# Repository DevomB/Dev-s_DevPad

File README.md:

# Dev's DevPad

This is my submission to HackPad to qualfiy for undercity. A 3-button macro pad with rotary encoder designed for real-world productivity.

## Features

XIAO RP2040

3× MX-style switches

Button 1: Open Terminal

Button 2: Screenshot to clipboard

Button 3: Force-close active window

1× EC11 Rotary Encoder

Rotate: Switch browser tabs (Ctrl+Tab / Ctrl+Shift+Tab)

Press: Open Task Manager (Ctrl+Shift+Esc)

## BOM

1x Seeed XIAO RP2040

3x MX-Style switches (used for Button 1, Button 2, Button 3)

1x EC11 Rotary encoder

Blank DSA keycaps (White) - for your buttons

M3x16mm screws & M3x5mx4mm heatset inserts - for mounting in your 3D printed case

## Firmware

The macropad's core functionality is powered by KMK Firmware, a powerful and flexible open-source keyboard firmware written in CircuitPython. This translates physical interactions into precise keyboard commands for the host computer.

## Images

### PCB

### CAD

### Assembly Images

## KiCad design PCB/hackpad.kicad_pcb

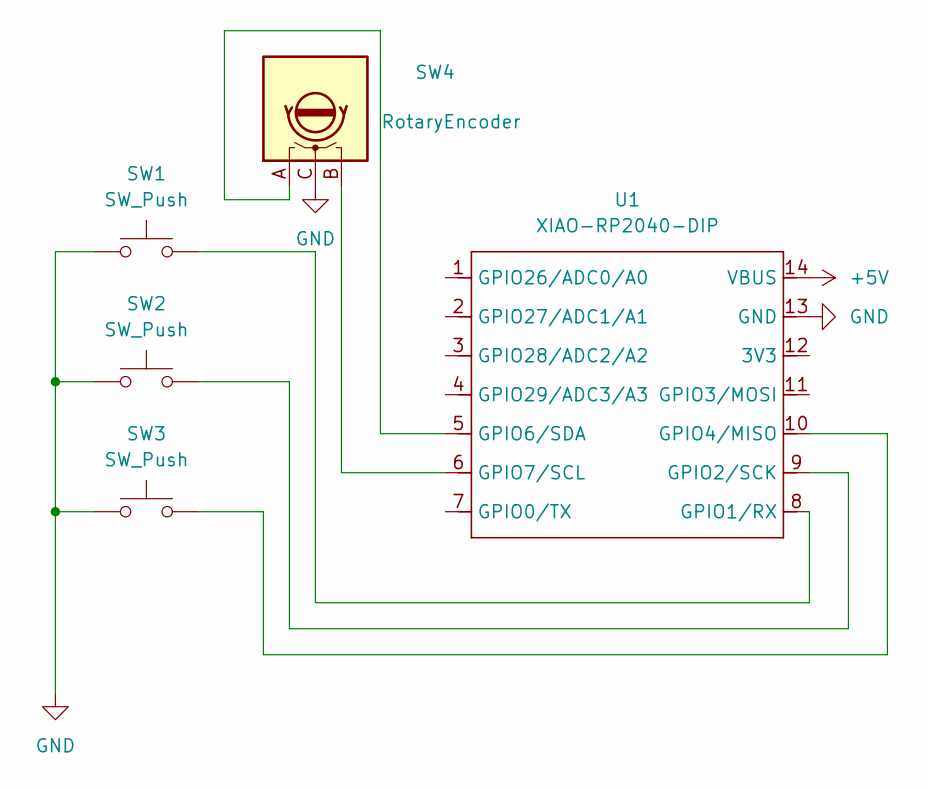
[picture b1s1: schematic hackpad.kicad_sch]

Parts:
SW1, SW2, SW3: SW_Push; SW_Cherry_MX_1.00u_PCB
SW4: RotaryEncoder; RotaryEncoder_Alps_EC11E-Switch_Vertical_H20mm
U1: XIAO-RP2040-DIP

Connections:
+5V: U1.14 (VBUS)
GND: SW1.1, SW2.1, SW3.1, SW4.C, U1.13 (GND)
unnamed: SW1.2, U1.8 (GPIO1/RX)
unnamed: SW2.2, U1.9 (GPIO2/SCK)
unnamed: SW3.2, U1.10 (GPIO4/MISO)
unnamed: SW4.A, U1.5 (GPIO6/SDA)
unnamed: SW4.B, U1.6 (GPIO7/SCL)

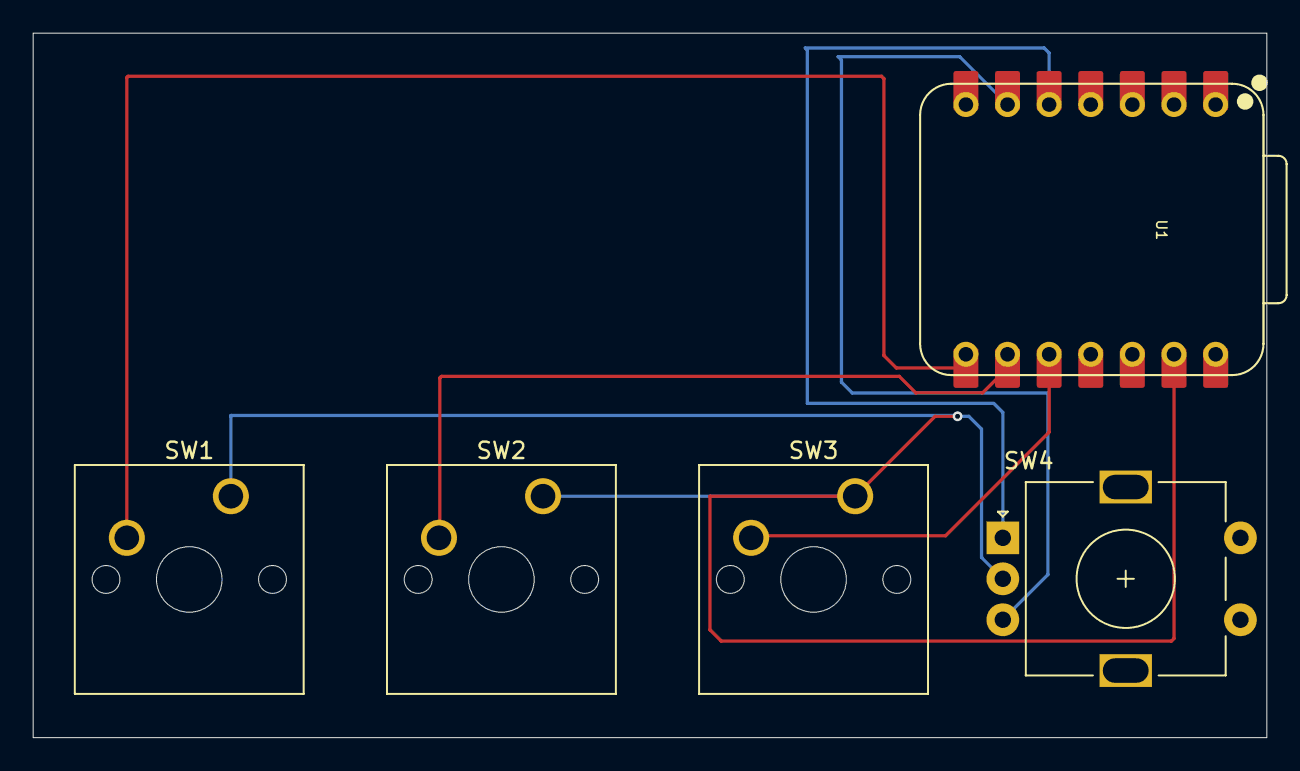
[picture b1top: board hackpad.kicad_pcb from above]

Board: 2 copper layers, 75.3 x 43.0 mm, 5 parts (0 on the bottom side), 6 nets.

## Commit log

2025-07-10 Final Commit Before CAD
2025-07-10 Added DevPad Cad file
2025-07-10 Commit before adding images to README
2025-07-10 Final Touch on README but need one more thing
2025-07-10 Added top file and photo
2025-07-10 Final Commit
2025-07-10 Change for Logan, made a new case new PCB
2025-07-10 Added Assembly Images
2025-07-11 Added a rounded plate case for ACON
2025-07-11 Changed CADA Images
